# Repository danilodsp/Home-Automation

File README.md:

# Home-Automation
Smart home system

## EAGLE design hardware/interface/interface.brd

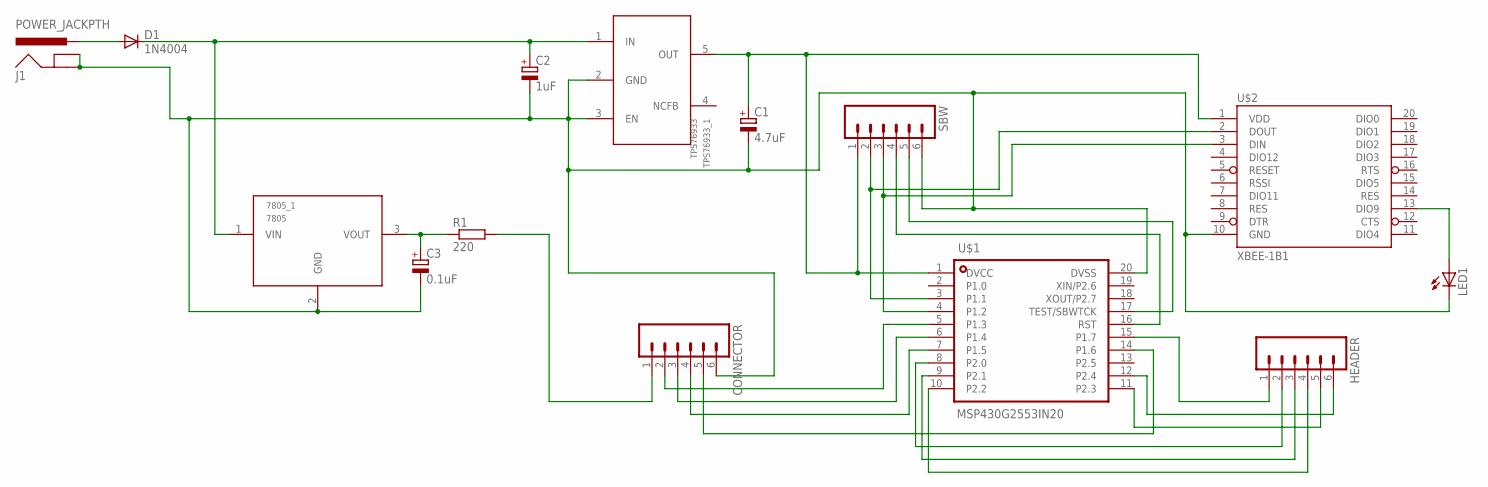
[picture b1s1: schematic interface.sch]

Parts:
7805_1: 7805; TO-220
C1: 4.7uF; E1,8-4
C2: 1uF; E1,8-4
C3: 0.1uF; E1,8-4
CONNECTOR: M06_90SIP; 1X06_90
D1: 1N4004; DO41-10
HEADER: M06_180SIP; 1X06_180
J1: POWER_JACKPTH; POWER_JACK_PTH
LED1: LED3MM
R1: 220; 0204/7
SBW: M06_180SIP; 1X06_180
TPS76933_1: TPS76933; SOT23-5
U$1: MSP430G2553IN20; DIP20
U$2: XBEE-1B1; XBEE-1

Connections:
GND: 7805_1.2 (GND), C1.-, C2.-, C3.-, CONNECTOR.6, J1.GND, J1.GNDBREAK, LED1.K (C), SBW.6, TPS76933_1.2 (GND), TPS76933_1.3 (EN), U$1.20 (DVSS), U$2.10 (GND)
unnamed: CONNECTOR.3, U$1.6 (P1.4)
unnamed: CONNECTOR.2, U$1.5 (P1.3)
unnamed: CONNECTOR.4, U$1.7 (P1.5)
unnamed: SBW.4, U$1.16 (RST)
unnamed: SBW.5, U$1.17 (TEST/SBWTCK)
unnamed: CONNECTOR.5, U$1.14 (P1.6)
unnamed: D1.A, J1.PWR
unnamed: LED1.A, U$2.13 (DIO9)
unnamed: 7805_1.1 (VIN), C2.+, D1.C, TPS76933_1.1 (IN)
unnamed: 7805_1.3 (VOUT), C3.+, R1.1
unnamed: HEADER.1, U$1.15 (P1.7)
unnamed: HEADER.2, U$1.8 (P2.0)
unnamed: HEADER.3, U$1.9 (P2.1)
unnamed: HEADER.4, U$1.10 (P2.2)
unnamed: HEADER.5, U$1.11 (P2.3)
unnamed: HEADER.6, U$1.12 (P2.4)
UART_1: SBW.2, U$1.3 (P1.1), U$2.2 (DOUT)
UART_2: SBW.3, U$1.4 (P1.2), U$2.3 (DIN)
VCC_3V: C1.+, SBW.1, TPS76933_1.5 (OUT), U$1.1 (DVCC), U$2.1 (VDD)
VCC_5V: CONNECTOR.1, R1.2

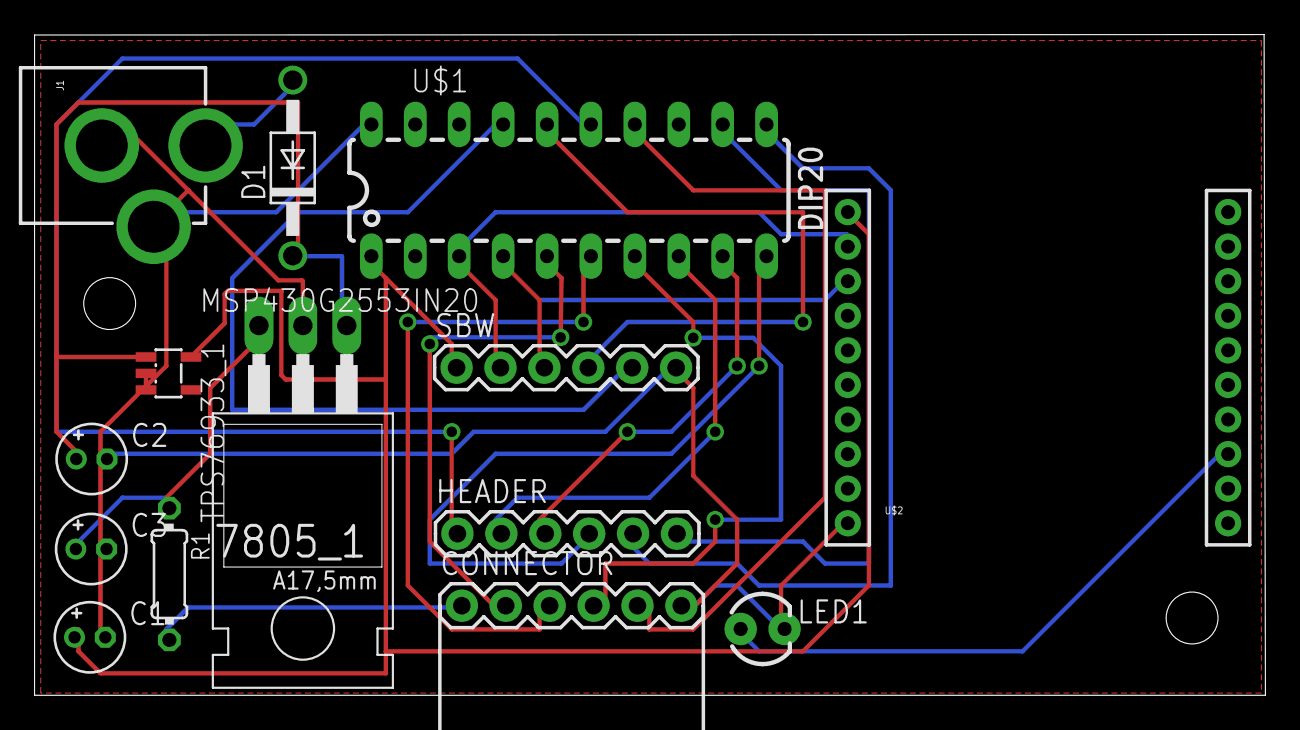
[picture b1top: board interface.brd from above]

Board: 2 copper layers, 71.2 x 38.2 mm, 14 parts (0 on the bottom side), 21 nets.

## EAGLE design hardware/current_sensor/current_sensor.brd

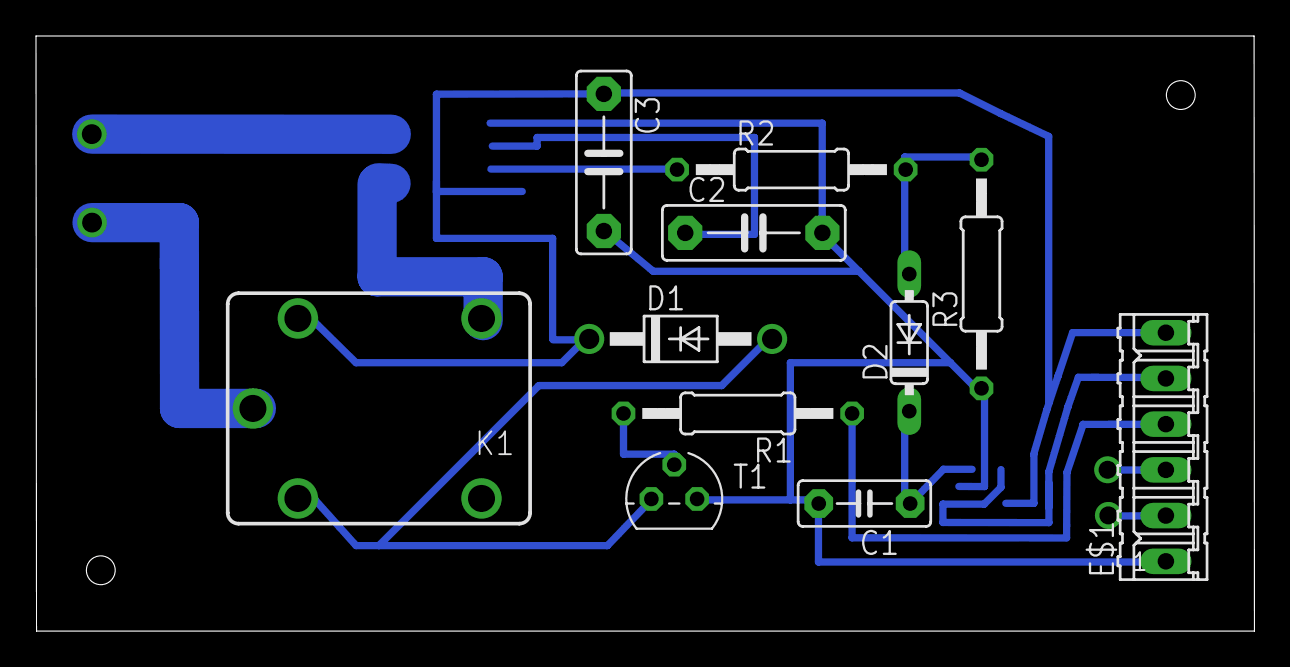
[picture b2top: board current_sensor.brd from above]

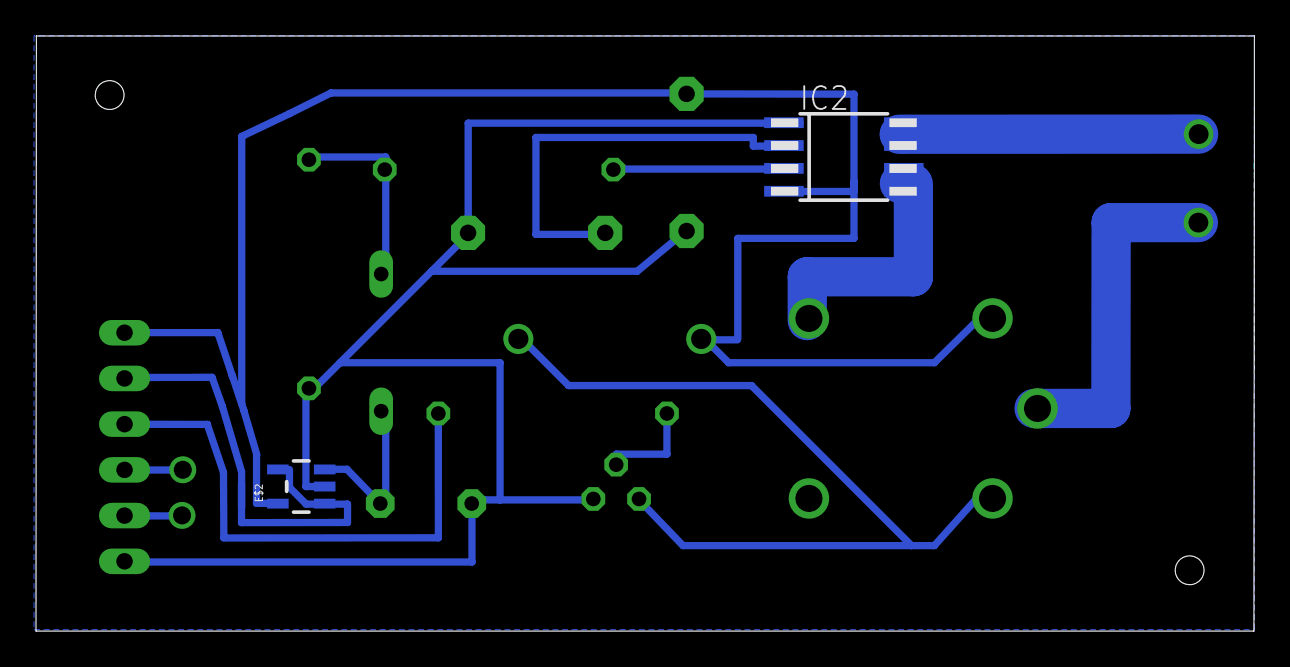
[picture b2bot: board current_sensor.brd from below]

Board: 2 copper layers, 67.7 x 33.1 mm, 13 parts (2 on the bottom side), 6 nets.

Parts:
C1: C5B2.5
C2, C3: C7.5B3
D1: 1N4004; DO41-10
D2: 1N4148DO35-7; DO35-7
E$1: 06P
E$2: SOT23-5
IC2: 24-AA65SM; SO-08M
K1: CQ1-12V; CQ1
R1, R2, R3: 0207/12
T1: BC547; TO92

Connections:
GND: C1.2, C2.2, C3.2, R3.1, T1.1
unnamed: D1.A, K1.2
unnamed: R1.2, T1.2
unnamed: D2.A, R3.2
unnamed: C1.1, D2.C
S$2: D1.C, K1.1

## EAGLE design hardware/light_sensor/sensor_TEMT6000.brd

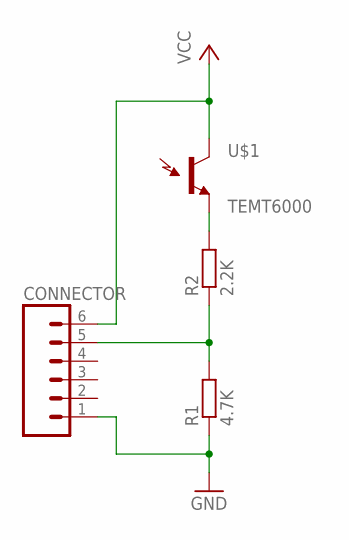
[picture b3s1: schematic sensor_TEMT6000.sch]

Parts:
CONNECTOR: M06_90SIP; 1X06_90
R1: 4.7K; 0204/7
R2: 2.2K; 0204/7
U$1: TEMT6000; TEMT6000-SEN

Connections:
GND: CONNECTOR.1, R1.1
unnamed: R2.2, U$1.EMITTER (E1)
SIG: CONNECTOR.5, R1.2, R2.1
VCC: CONNECTOR.6, U$1.COLLECTOR (C1)

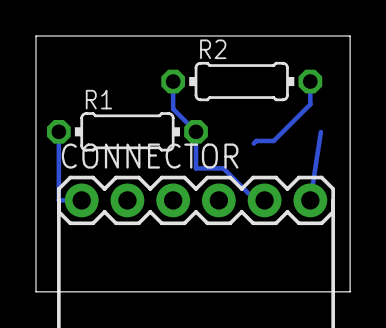
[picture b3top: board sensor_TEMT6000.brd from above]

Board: 2 copper layers, 17.4 x 14.2 mm, 4 parts (1 on the bottom side), 4 nets.

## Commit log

2019-08-27 Added firmware of home automation project
2019-08-27 Integration test
2019-08-29 Added test current sensor
2019-08-29 Hardware boards added

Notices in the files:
parts and their libraries:
SparkFun: Licensing: CC v3.0 Share-Alike You are welcome to use this library for commercial purposes.
